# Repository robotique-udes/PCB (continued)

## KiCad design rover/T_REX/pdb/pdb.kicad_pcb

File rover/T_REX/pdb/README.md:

# PDB (Power Distribution Board)
PCB servant à gérer la distribution de puissance électrique

Voici les informations concernant le PCB : PDB 

## Image du PCB en 3D

## Objectifs:
* Protéger tous les autres boards du Over/Under Voltage pour le 5V, 12V et 24V
* Agir en tant que POE pour les cameras branché en Ethernet
* Diriger le signal des cameras sur les bonnes pins selon la norme Ethernet
* Agir en tant que POE pour les antennes
* Alimenter des accessoires 12V par 2 connecteurs Ethernet en utilisant les pins 7 (12V) et 8 (GND)
* Permettre de pouvoir sortir une des 3 tension par un screw terminal
* Communiquer par le CAN BUS
* Sélectionner avec les GPIO les cameras qui doivent recevoir du power

## Composants principaux:
* ESP32 DEV KIT V1
* TJA1050 (CAN BUS)
* LTC4365 (Over/Under Voltage protaction)
* DMG4822SSD (proche du LTC4365)
* DELs
* CLP6C-FKB-CKNPRGJBB7A363 (ERROR DEL)
* Boutons
* Horizontal Amphenol 54602 RJ45
* AMASS XT60PW-M Power connectors
* ASSMANN_A-2014 Ethernet connector
* CRJ036-5-TH_2x4 Ethernet connector
* BTS5200 (4 Channel Mosfet)

## Fonctionnement:
Le PDB reçoit 3 tensions en entrée, du 5V, du 12V et du 24V.
Le 12V sert principalement pour alimenter les caméras qui sont alimentés avec un POE avec un Pinout spécial. Il sert aussi à alimenter 2 accessoires potentiels.
Le 24V sert à alimenter le les antennes qui sont sur le Rover.
Puis le 5V sert à alimenter les autres PCBs qui sont sur le Rover en POE avec un Pinout spécial. 
Le circuit sécurise les trois tensions contre les sur-tensions et le drops de tensions.
Le circuit communique en CAN bus avec les autres circuits sur le Rover et vers l'ordi principal.

## PGIO
### Outputs

Name         | GPIO
---          | ---
CAM_SIGN_0   | D18
CAM_SIGN_1   | D19
CAM_SIGN_2   | D33
CAM_SIGN_3   | D32
PWM_0        | D21
PWM_1        | D22
ACC1_CONTROL | D23
ACC2_CONTROL | D25
LED_R        | D14
LED_G        | D27
LED_B        | D26

### Communication

Name    | GPIO
---     | ---
TXC    | D6
RXC    | D7

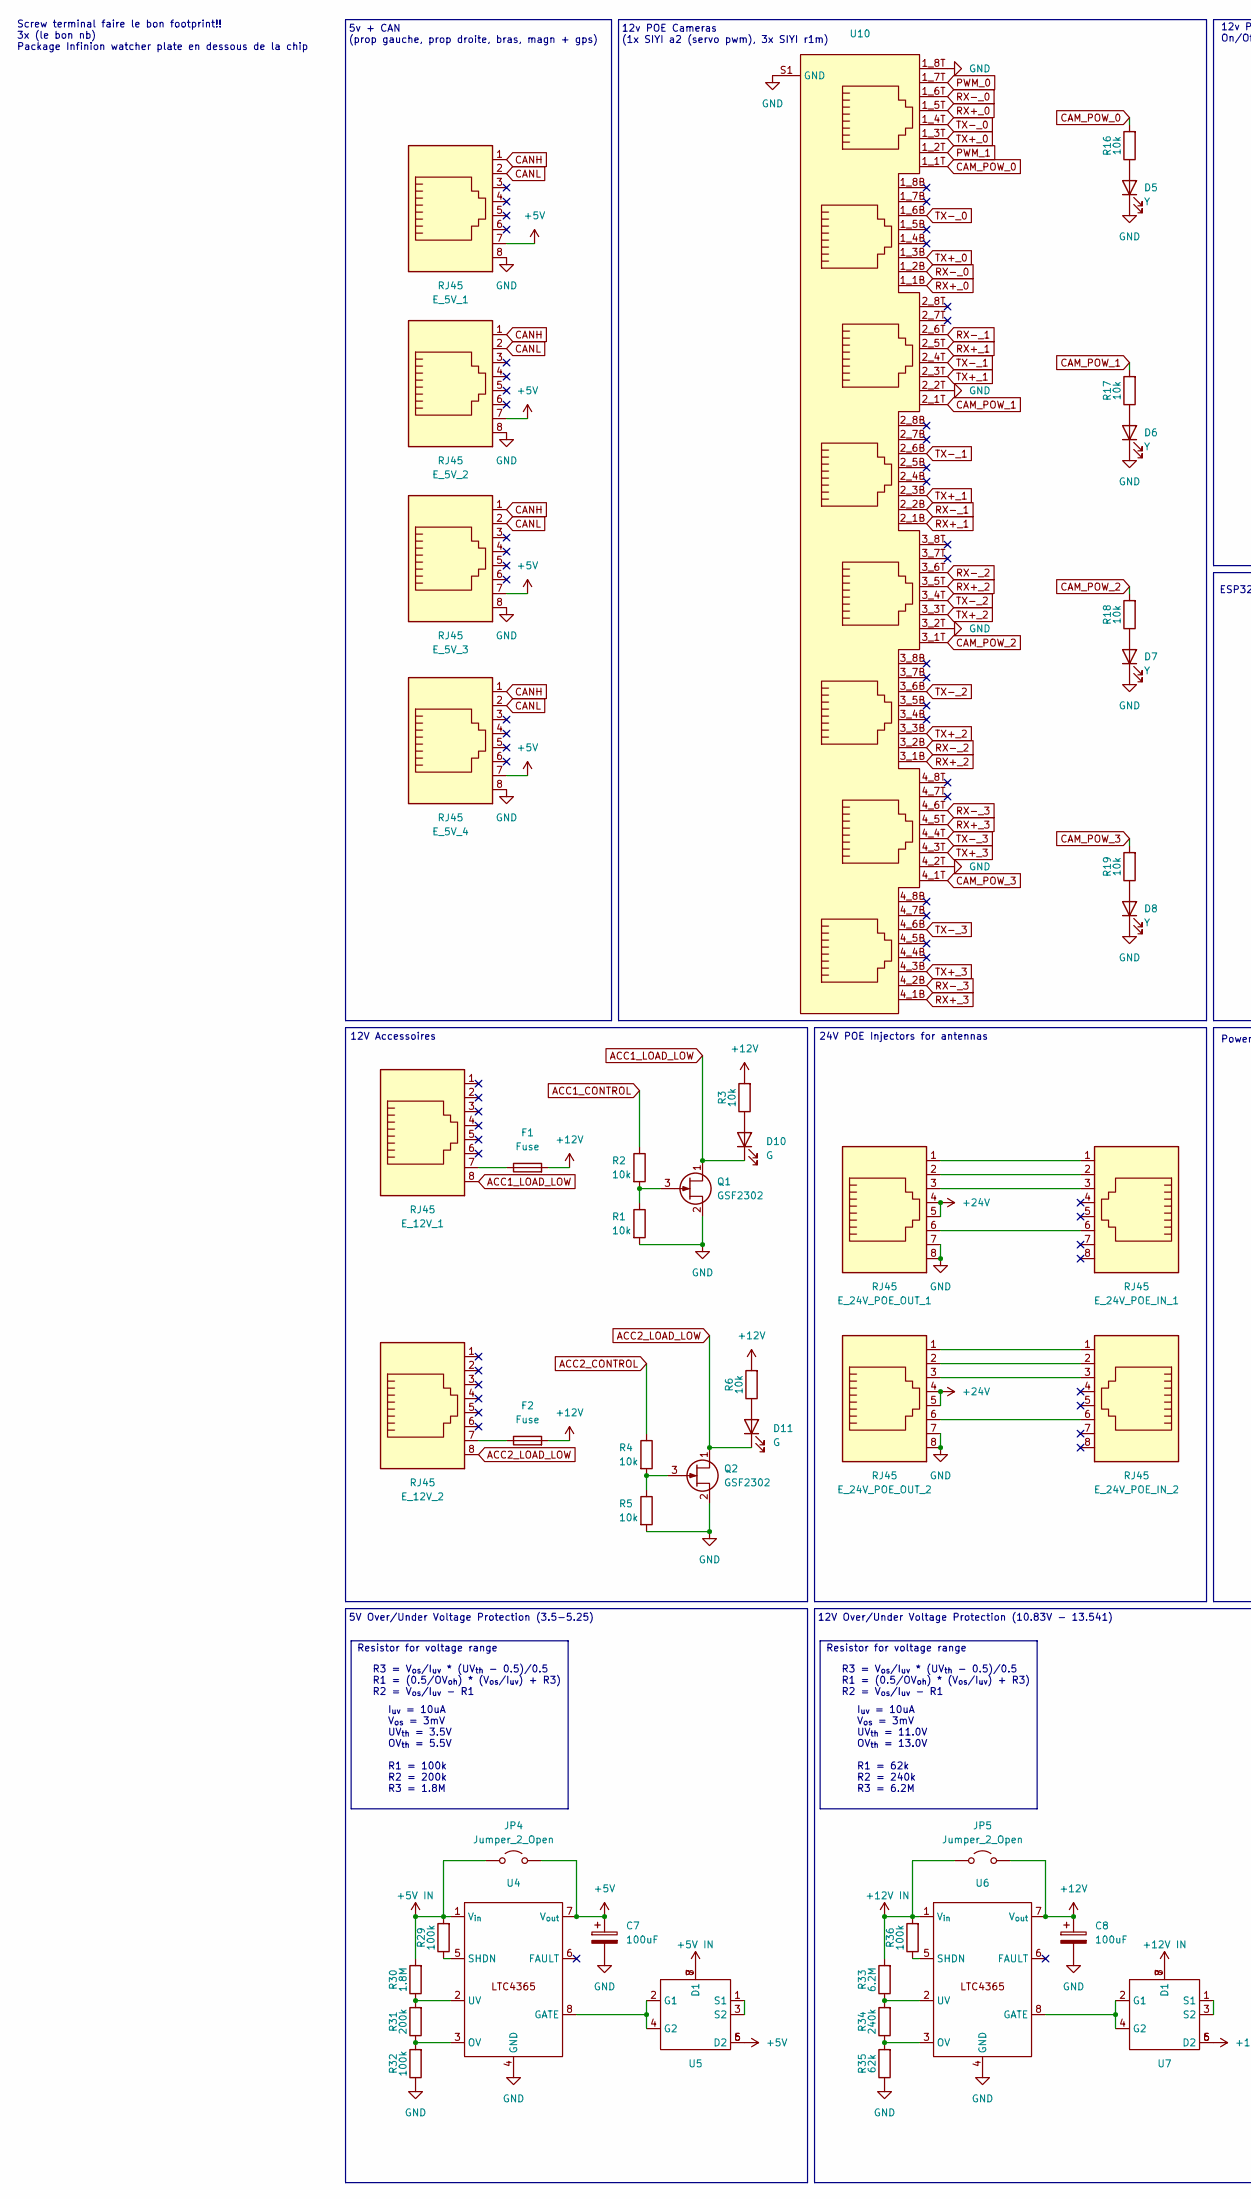
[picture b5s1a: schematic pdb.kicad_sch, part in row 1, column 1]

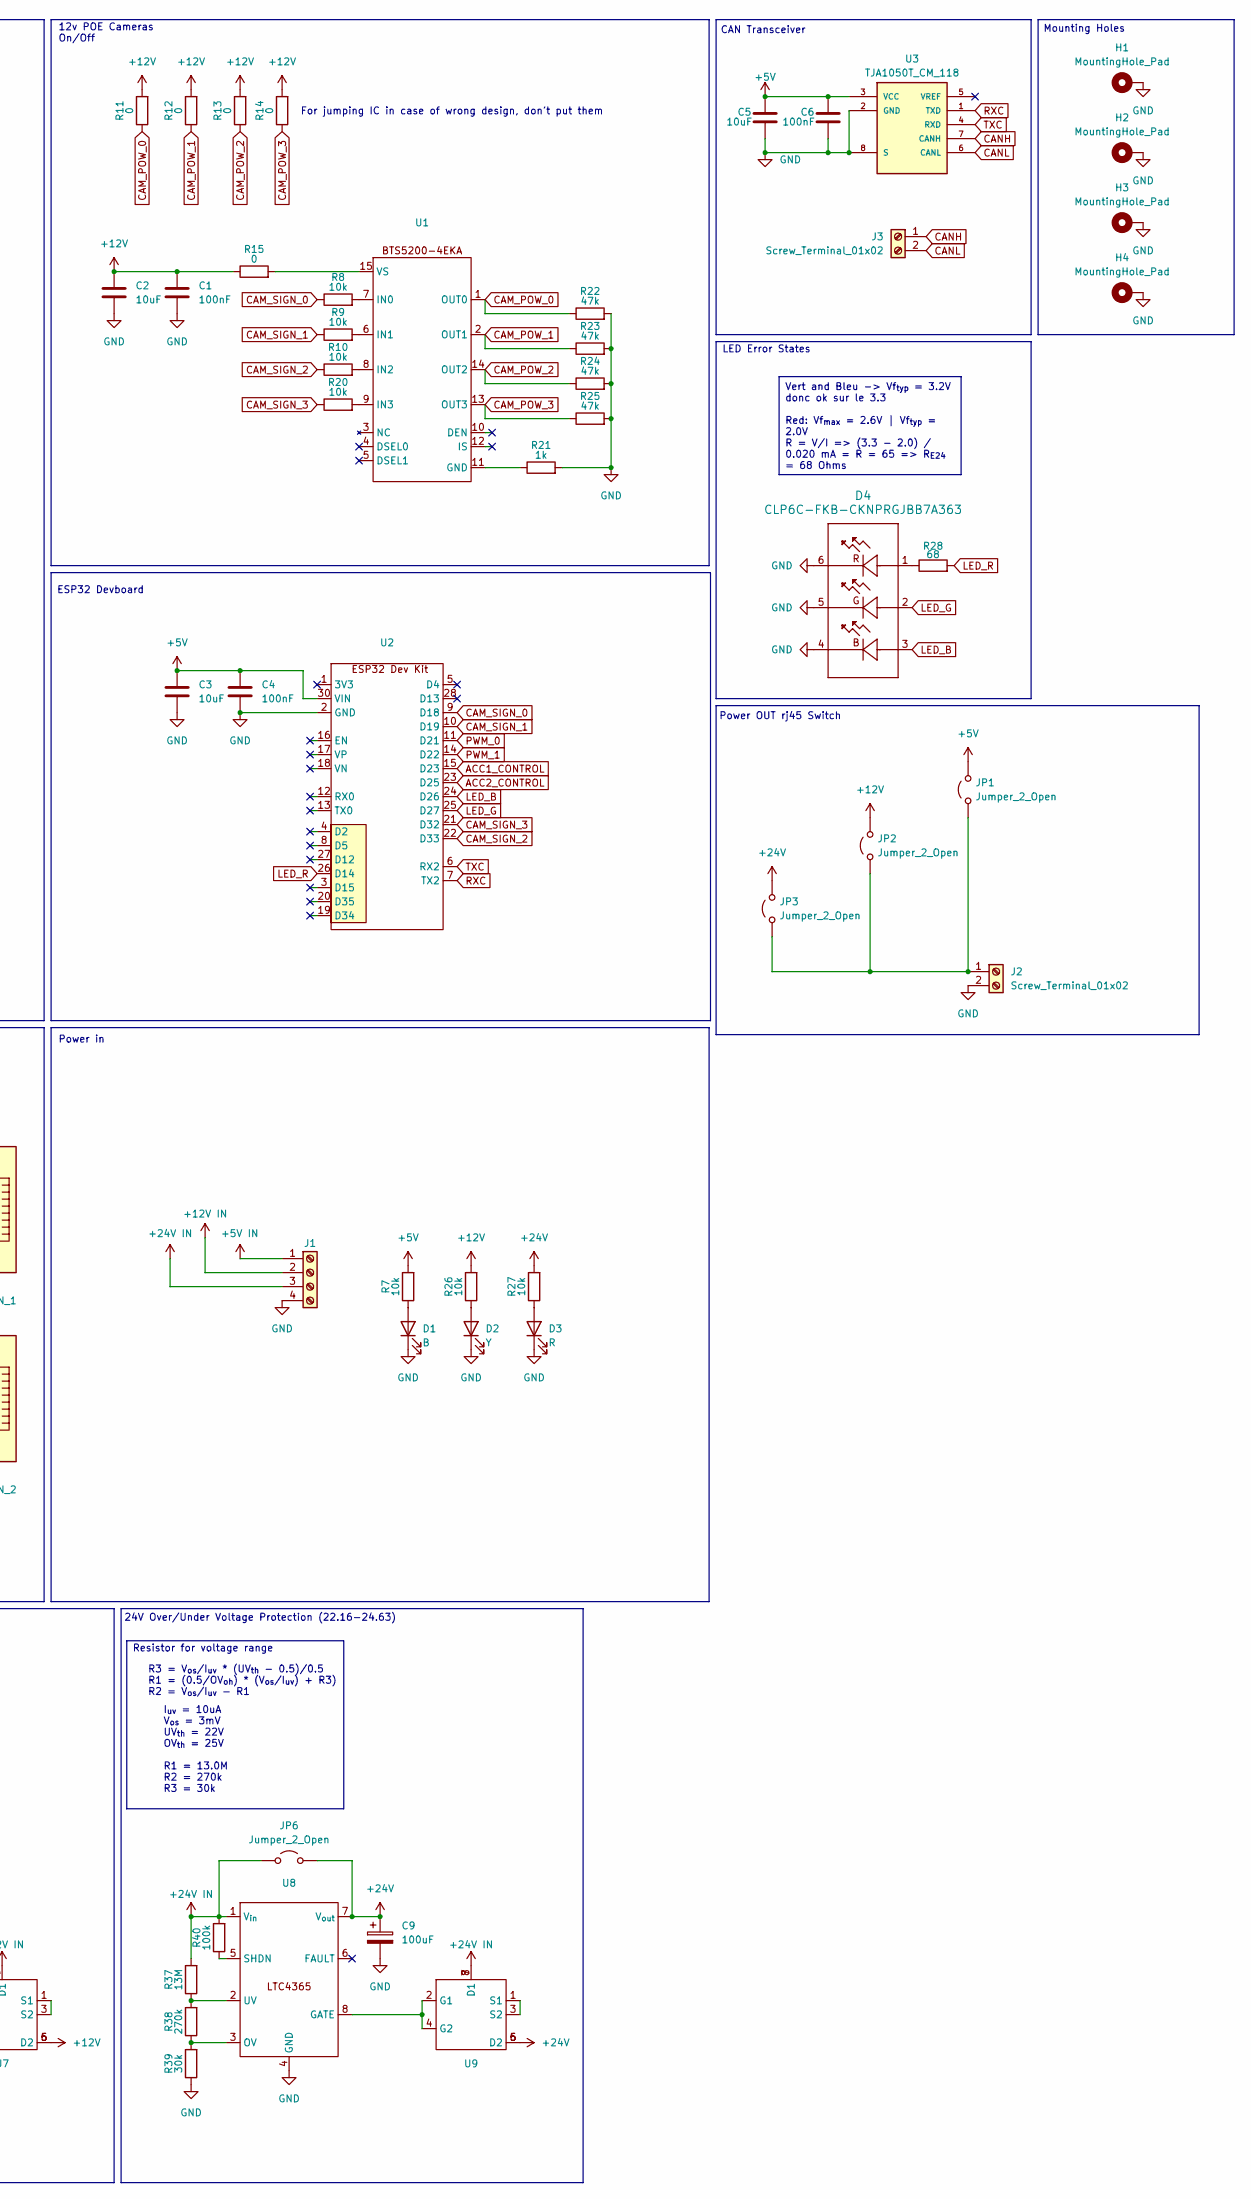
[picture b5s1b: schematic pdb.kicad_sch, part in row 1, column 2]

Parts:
C1, C4, C6: 100nF; C_0805_2012Metric_Pad1.18x1.45mm_HandSolder
C2, C3, C5: 10uF; C_0805_2012Metric_Pad1.18x1.45mm_HandSolder
C7, C8, C9: 100uF; CP_Radial_D5.0mm_P2.00mm
D1: B; LED_0805_2012Metric_Pad1.15x1.40mm_HandSolder
D2, D5, D6, D7, D8: Y; LED_0805_2012Metric_Pad1.15x1.40mm_HandSolder
D3: R; LED_0805_2012Metric_Pad1.15x1.40mm_HandSolder
D4: CLP6C-FKB-CKNPRGJBB7A363; CLP6C-FKB-CKNPRGJBB7A363_CRE-M
D10, D11: G; LED_0805_2012Metric_Pad1.15x1.40mm_HandSolder
E_5V_1, E_5V_2, E_5V_3, E_5V_4, E_12V_2, E_24V_POE_IN_2: RJ45; AMPHENOL_54601-908WPLF
E_12V_1, E_24V_POE_IN_1, E_24V_POE_OUT_1, E_24V_POE_OUT_2: RJ45; ASSMANN_A-2014-2-4-N-T-R
F1, F2: Fuse; FUSE_3568-20
H1, H2, H3, H4: MountingHole_Pad; MountingHole_3.2mm_M3_DIN965_Pad_TopBottom
J1: Screw_Terminal_01x04; PHOENIX_1790335_4pin
J2, J3: Screw_Terminal_01x02; PHOENIX_1790335_2pin
JP1, JP2, JP3, JP4, JP5, JP6: Jumper_2_Open; PinHeader_1x02_P2.54mm_Vertical
Q1, Q2: GSF2302; SOT-23_Handsoldering
R1, R2, R3, R4, R5, R6, R7, R8, R9, R10, R16, R17, R18, R19, R20, R26, R27: 10k; R_0805_2012Metric_Pad1.20x1.40mm_HandSolder
R11, R12, R13, R14, R15: 0; R_0805_2012Metric_Pad1.20x1.40mm_HandSolder
R21: 1k; R_0805_2012Metric_Pad1.20x1.40mm_HandSolder
R22, R23, R24, R25: 47k; R_0805_2012Metric_Pad1.20x1.40mm_HandSolder
R28: 68; R_0805_2012Metric_Pad1.20x1.40mm_HandSolder
R29, R32, R36, R40: 100k; R_0805_2012Metric_Pad1.20x1.40mm_HandSolder
R30: 1.8M; R_0805_2012Metric_Pad1.20x1.40mm_HandSolder
R31: 200k; R_0805_2012Metric_Pad1.20x1.40mm_HandSolder
R33: 6.2M; R_0805_2012Metric_Pad1.20x1.40mm_HandSolder
R34: 240k; R_0805_2012Metric_Pad1.20x1.40mm_HandSolder
R35: 62k; R_0805_2012Metric_Pad1.20x1.40mm_HandSolder
R37: 13M; R_0805_2012Metric_Pad1.20x1.40mm_HandSolder
R38: 270k; R_0805_2012Metric_Pad1.20x1.40mm_HandSolder
R39: 30k; R_0805_2012Metric_Pad1.20x1.40mm_HandSolder
U1: SOIC-14_3.9x8.7mm_P1.27mm
U2: MODULE_ESP32_DEVKIT_V1
U3: TJA1050T_CM_118; SOIC127P600X175-8N; PARTREV 4
U4, U6, U8: TSOT-23-8_HandSoldering
U5, U7, U9: SOIC-8-1EP_3.9x4.9mm_P1.27mm_hand_solder
U10: CUI_CRJ036-5-TH

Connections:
+5V: C3.1, C4.1, C5.1, C6.1, C7.1, E_5V_1.7, E_5V_2.7, E_5V_3.7, E_5V_4.7, JP1.2 (B), JP4.2 (B), R7.2, U2.30 (VIN), U3.3 (VCC), U4.7 (V_{out}), U5.5 (D2), U5.6 (D2)
+5V IN: J1.1, JP4.1 (A), R29.2, R30.2, U4.1 (V_{in}), U5.7 (D1), U5.8 (D1)
+12V: C1.1, C2.1, C8.1, F1.2, F2.2, JP2.2 (B), JP5.2 (B), R3.2, R6.2, R11.2, R12.2, R13.2, R14.2, R15.1, R26.2, U6.7 (V_{out}), U7.5 (D2), U7.6 (D2)
+12V IN: J1.2, JP5.1 (A), R33.2, R36.2, U6.1 (V_{in}), U7.7 (D1), U7.8 (D1)
+24V: C9.1, E_24V_POE_OUT_1.4, E_24V_POE_OUT_1.5, E_24V_POE_OUT_2.4, E_24V_POE_OUT_2.5, JP3.2 (B), JP6.2 (B), R27.2, U8.7 (V_{out}), U9.5 (D2), U9.6 (D2)
+24V IN: J1.3, JP6.1 (A), R37.2, R40.2, U8.1 (V_{in}), U9.7 (D1), U9.8 (D1)
ACC1_CONTROL: R2.1, U2.15 (D23)
ACC1_LOAD_LOW: D10.1 (K), E_12V_1.8, Q1.1 (D)
ACC2_CONTROL: R4.1, U2.23 (D25)
ACC2_LOAD_LOW: D11.1 (K), E_12V_2.8, Q2.1 (D)
CAM_POW_0: R11.1, R16.2, R22.1, U1.1 (OUT0), U10.1_1T
CAM_POW_1: R12.1, R17.2, R23.1, U1.2 (OUT1), U10.2_1T
CAM_POW_2: R13.1, R18.2, R24.1, U1.14 (OUT2), U10.3_1T
CAM_POW_3: R14.1, R19.2, R25.1, U1.13 (OUT3), U10.4_1T
CAM_SIGN_0: R8.1, U2.9 (D18)
CAM_SIGN_1: R9.1, U2.10 (D19)
CAM_SIGN_2: R10.1, U2.22 (D33)
CAM_SIGN_3: R20.1, U2.21 (D32)
CANH: E_5V_1.1, E_5V_2.1, E_5V_3.1, E_5V_4.1, J3.1, U3.7 (CANH)
CANL: E_5V_1.2, E_5V_2.2, E_5V_3.2, E_5V_4.2, J3.2, U3.6 (CANL)
GND: C1.2, C2.2, C3.2, C4.2, C5.2, C6.2, C7.2, C8.2, C9.2, D1.1 (K), D2.1 (K), D3.1 (K), D4.4, D4.5, D4.6, D5.1 (K), D6.1 (K), D7.1 (K), D8.1 (K), E_5V_1.8, E_5V_2.8, E_5V_3.8, E_5V_4.8, E_24V_POE_OUT_1.7, E_24V_POE_OUT_1.8, E_24V_POE_OUT_2.7, E_24V_POE_OUT_2.8, H1.1, H2.1, H3.1, H4.1, J1.4, J2.2, Q1.2 (S), Q2.2 (S), R1.2, R5.2, R21.2, R22.2, R23.2, R24.2, R25.2, R32.1, R35.1, R39.1, U2.2 (GND), U3.2 (GND), U3.8 (S), U4.4 (GND), U6.4 (GND), U8.4 (GND), U10.1_8T, U10.2_2T, U10.3_2T, U10.4_2T, U10.S1 (GND)
LED_B: D4.3, U2.24 (D26)
LED_G: D4.2, U2.25 (D27)
LED_R: R28.2, U2.26 (D14)
unnamed: D1.2 (A), R7.1
unnamed: D2.2 (A), R26.1
unnamed: D3.2 (A), R27.1
unnamed: D4.1, R28.1
unnamed: D5.2 (A), R16.1
unnamed: D6.2 (A), R17.1
unnamed: D7.2 (A), R18.1
unnamed: D8.2 (A), R19.1
unnamed: D10.2 (A), R3.1
unnamed: D11.2 (A), R6.1
unnamed: E_12V_1.7, F1.1
unnamed: E_12V_2.7, F2.1
unnamed: E_24V_POE_IN_1.1, E_24V_POE_OUT_1.1
unnamed: E_24V_POE_IN_1.2, E_24V_POE_OUT_1.2
unnamed: E_24V_POE_IN_1.3, E_24V_POE_OUT_1.3
unnamed: E_24V_POE_IN_1.6, E_24V_POE_OUT_1.6
unnamed: E_24V_POE_IN_2.1, E_24V_POE_OUT_2.1
unnamed: E_24V_POE_IN_2.2, E_24V_POE_OUT_2.2
unnamed: E_24V_POE_IN_2.3, E_24V_POE_OUT_2.3
unnamed: E_24V_POE_IN_2.6, E_24V_POE_OUT_2.6
unnamed: J2.1, JP1.1 (A), JP2.1 (A), JP3.1 (A)
unnamed: Q1.3 (G), R1.1, R2.2
unnamed: Q2.3 (G), R4.2, R5.1
unnamed: R21.1, U1.11 (GND)
unnamed: R8.2, U1.7 (IN0)
unnamed: R9.2, U1.6 (IN1)
unnamed: R10.2, U1.8 (IN2)
unnamed: R20.2, U1.9 (IN3)
unnamed: R15.2, U1.15 (VS)
unnamed: U4.8 (GATE), U5.2 (G1), U5.4 (G2)
unnamed: R31.1, R32.2, U4.3 (OV)
unnamed: R29.1, U4.5 (SHDN)
unnamed: R30.1, R31.2, U4.2 (UV)
unnamed: U5.1 (S1), U5.3 (S2)
unnamed: U6.8 (GATE), U7.2 (G1), U7.4 (G2)
unnamed: R34.1, R35.2, U6.3 (OV)
unnamed: R36.1, U6.5 (SHDN)
unnamed: R33.1, R34.2, U6.2 (UV)
unnamed: U7.1 (S1), U7.3 (S2)
unnamed: U8.8 (GATE), U9.2 (G1), U9.4 (G2)
unnamed: R38.1, R39.2, U8.3 (OV)
unnamed: R40.1, U8.5 (SHDN)
unnamed: R37.1, R38.2, U8.2 (UV)
unnamed: U9.1 (S1), U9.3 (S2)
PWM_0: U2.11 (D21), U10.1_7T
PWM_1: U2.14 (D22), U10.1_2T
RX+_0: U10.1_1B, U10.1_5T
RX+_1: U10.2_1B, U10.2_5T
RX+_2: U10.3_1B, U10.3_5T
RX+_3: U10.4_1B, U10.4_5T
RX-_0: U10.1_2B, U10.1_6T
RX-_1: U10.2_2B, U10.2_6T
RX-_2: U10.3_2B, U10.3_6T
RX-_3: U10.4_2B, U10.4_6T
RXC: U2.7 (TX2), U3.1 (TXD)
TX+_0: U10.1_3B, U10.1_3T
TX+_1: U10.2_3B, U10.2_3T
TX+_2: U10.3_3B, U10.3_3T
TX+_3: U10.4_3B, U10.4_3T
TX-_0: U10.1_4T, U10.1_6B
TX-_1: U10.2_4T, U10.2_6B
TX-_2: U10.3_4T, U10.3_6B
TX-_3: U10.4_4T, U10.4_6B
TXC: U2.6 (RX2), U3.4 (RXD)

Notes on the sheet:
Vert and Bleu -> Vf_{typ} = 3.2V donc ok sur le 3.3 Red: Vf_{max} = 2.6V | Vf_{typ} = 2.0V R = V/I => (3.3 - 2.0) / 0.020 mA = R = 65 => R_{E24} = 68 Ohms
5V Over/Under Voltage Protection (3.5-5.25)
Mounting Holes
CAN Transceiver
R3 = V_{os}/I_{uv} * (UV_{th} - 0.5)/0.5 R1 = (0.5/OV_{oh}) * (V_{os}/I_{uv}) + R3) R2 = V_{os}/I_{uv} - R1
LED Error States
24V Over/Under Voltage Protection (22.16-24.63)
Power in
24V POE Injectors for antennas
12V Over/Under Voltage Protection (10.83V - 13.541)
Screw terminal faire le bon footprint!! 3x (le bon nb) Package Infinion watcher plate en dessous de la chip
Resistor for voltage range
12v POE Cameras (1x SIYI a2 (servo pwm), 3x SIYI r1m)
I_{uv} = 10uA V_{os} = 3mV UV_{th} = 11.0V OV_{th} = 13.0V R1 = 62k R2 = 240k R3 = 6.2M
Power OUT rj45 Switch
5v + CAN (prop gauche, prop droite, bras, magn + gps)
For jumping IC in case of wrong design, don't put them
12V Accessoires
I_{uv} = 10uA V_{os} = 3mV UV_{th} = 22V OV_{th} = 25V R1 = 13.0M R2 = 270k R3 = 30k
12v POE Cameras On/Off
I_{uv} = 10uA V_{os} = 3mV UV_{th} = 3.5V OV_{th} = 5.5V R1 = 100k R2 = 200k R3 = 1.8M
ESP32 Devboard

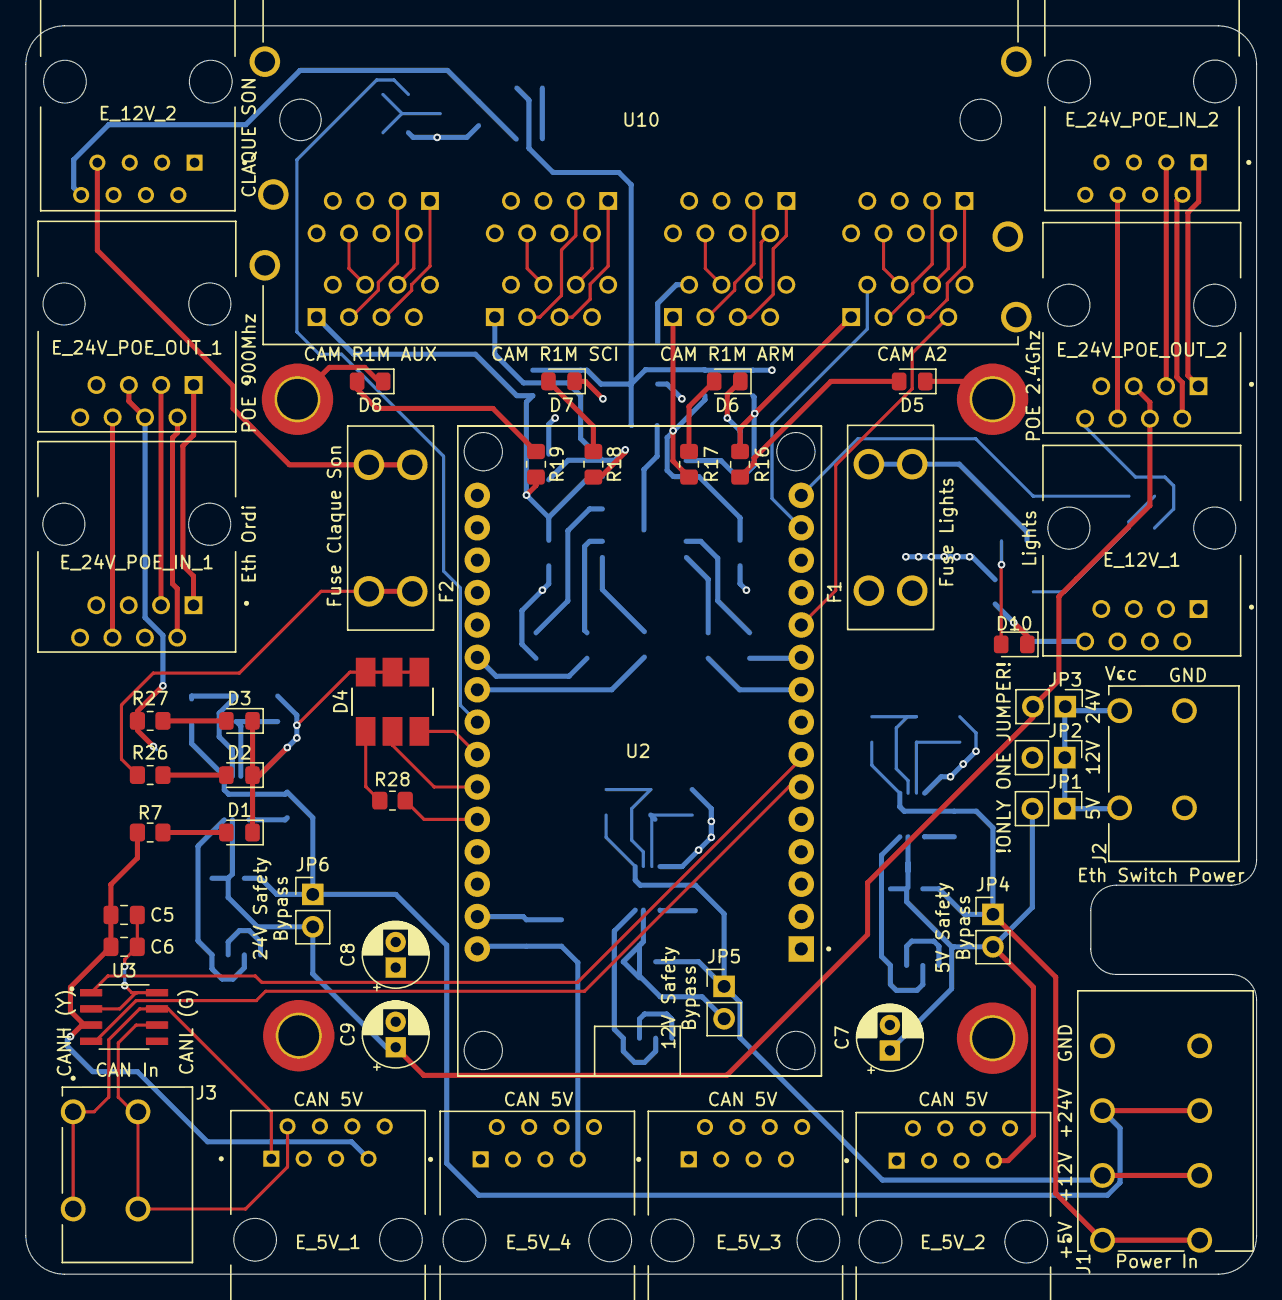
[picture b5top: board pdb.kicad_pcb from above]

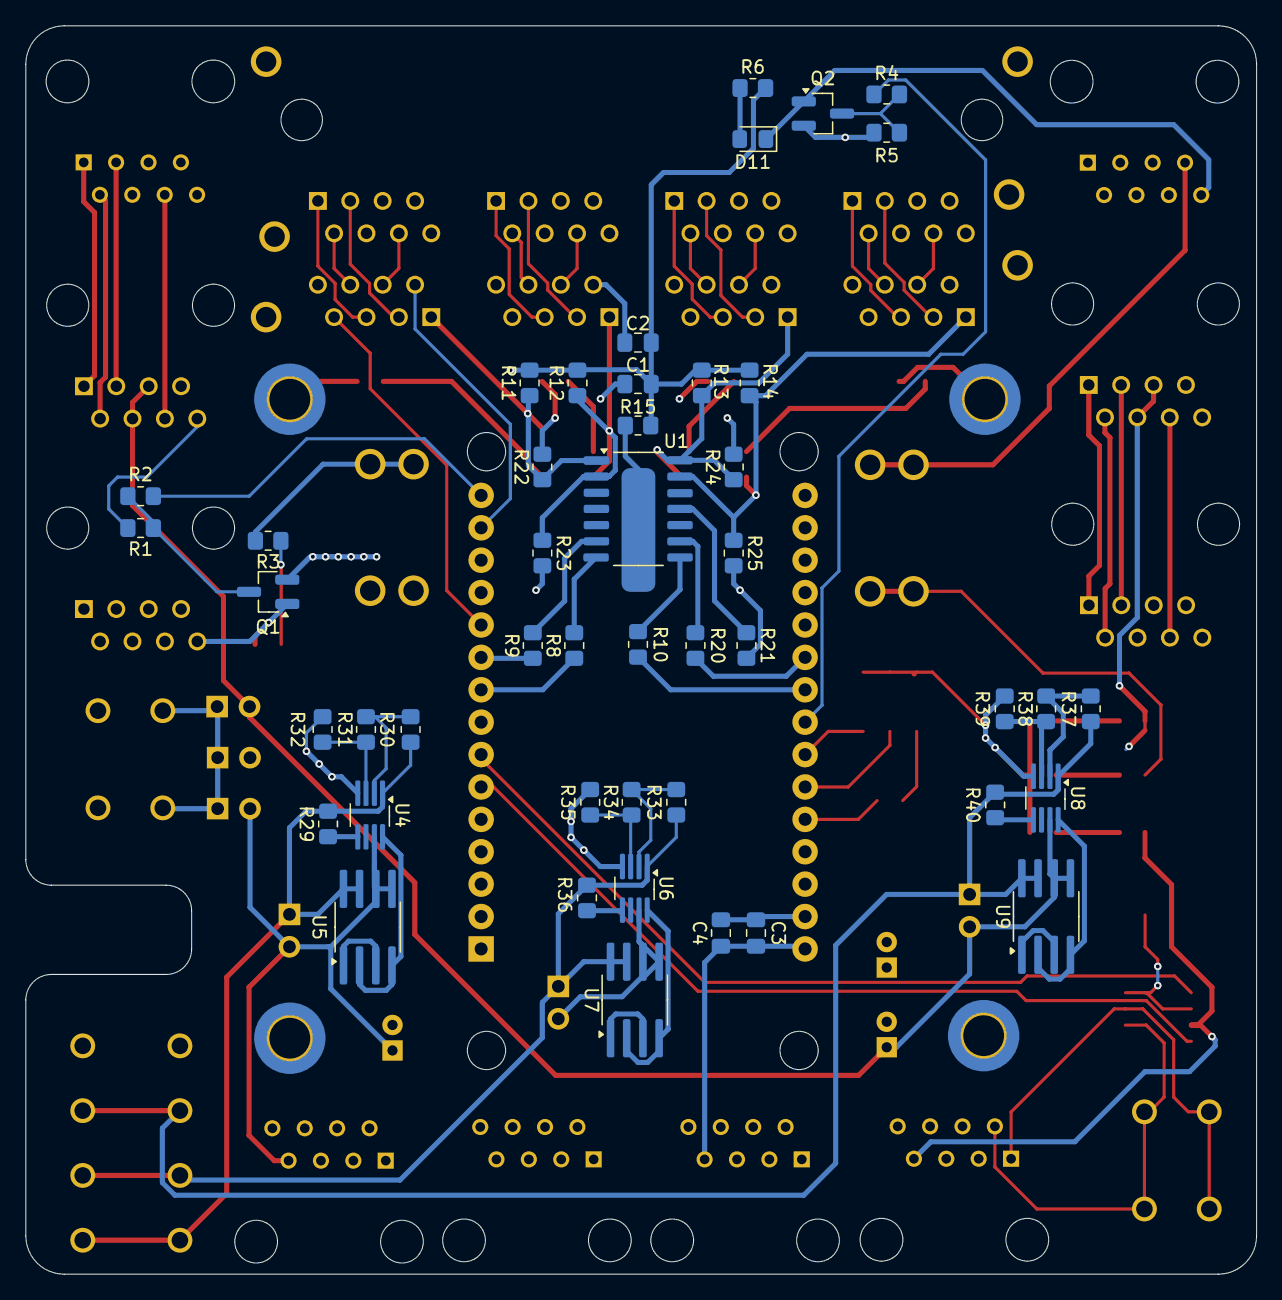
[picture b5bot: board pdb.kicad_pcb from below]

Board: 4 copper layers, 96.5 x 97.9 mm, 96 parts (46 on the bottom side), 88 nets.

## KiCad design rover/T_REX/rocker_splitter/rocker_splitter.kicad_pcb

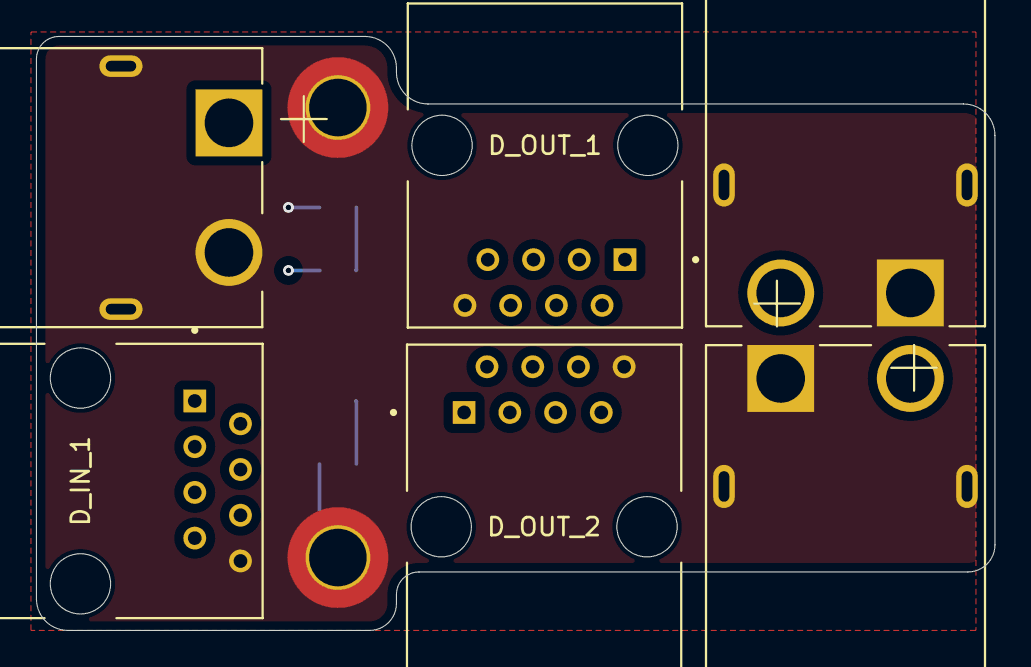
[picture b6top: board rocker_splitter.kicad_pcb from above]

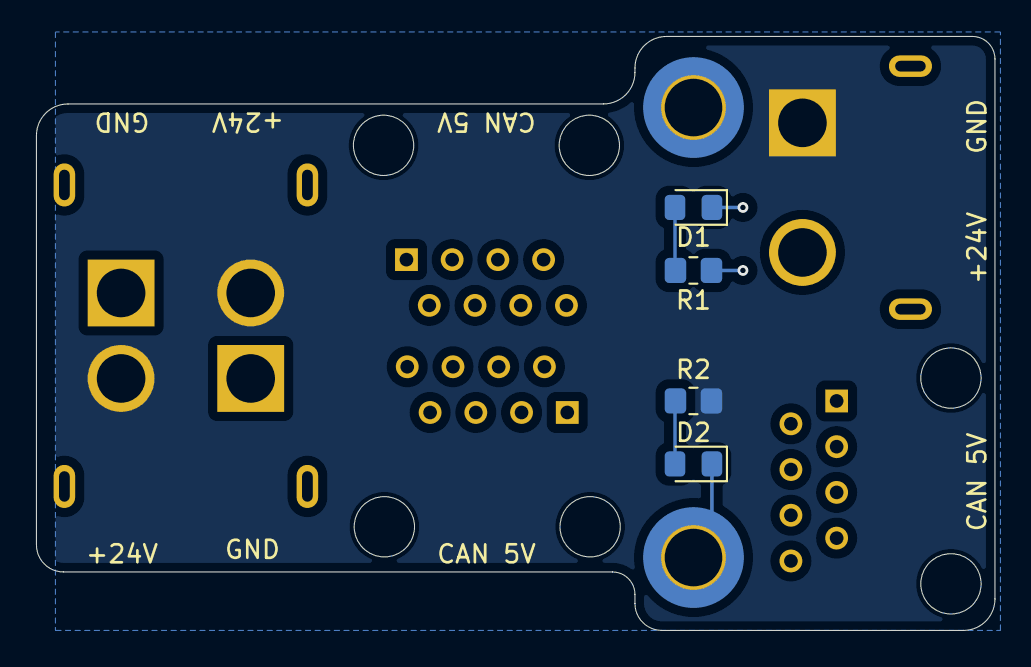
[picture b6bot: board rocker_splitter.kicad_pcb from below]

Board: 4 copper layers, 53.2 x 33.0 mm, 12 parts (4 on the bottom side), 7 nets.

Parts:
D1: G; LED_0805_2012Metric_Pad1.15x1.40mm_HandSolder
D2: B; LED_0805_2012Metric_Pad1.15x1.40mm_HandSolder
D_IN_1: RJ45; AMPHENOL_54601-908WPLF
D_OUT_1, D_OUT_2: RJ45; AMPHENOL_54601-908WPLF
H1, H2: MountingHole_Pad; MountingHole_3.2mm_M3_DIN965_Pad_TopBottom
P_IN_1: XT60PW-M; AMASS_XT60PW-M
P_OUT_1, P_OUT_2: XT60PW-M; AMASS_XT60PW-M
R1, R2: 10k; R_0805_2012Metric_Pad1.20x1.40mm_HandSolder

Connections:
+5V: D_IN_1.7, D_OUT_1.7, D_OUT_2.7, R1.1
+24V: P_IN_1.1 (+), P_OUT_1.2 (-), P_OUT_2.2 (-), R2.1
CANH: D_IN_1.1, D_OUT_1.1, D_OUT_2.1
CANL: D_IN_1.2, D_OUT_1.2, D_OUT_2.2
GND: D1.1 (K), D2.1 (K), D_IN_1.8, D_OUT_1.8, D_OUT_2.8, H1.1, H2.1, P_IN_1.2, P_OUT_1.1 (+), P_OUT_1.2, P_OUT_2.1 (+), P_OUT_2.2
unnamed: D1.2 (A), R1.2
unnamed: D2.2 (A), R2.2
